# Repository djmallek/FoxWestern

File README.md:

# FoxWestern
This is for a rocketry project.  It uses tracking, remote, and onboard logging to keep track of the rocket's location and howmany G's it pulls.

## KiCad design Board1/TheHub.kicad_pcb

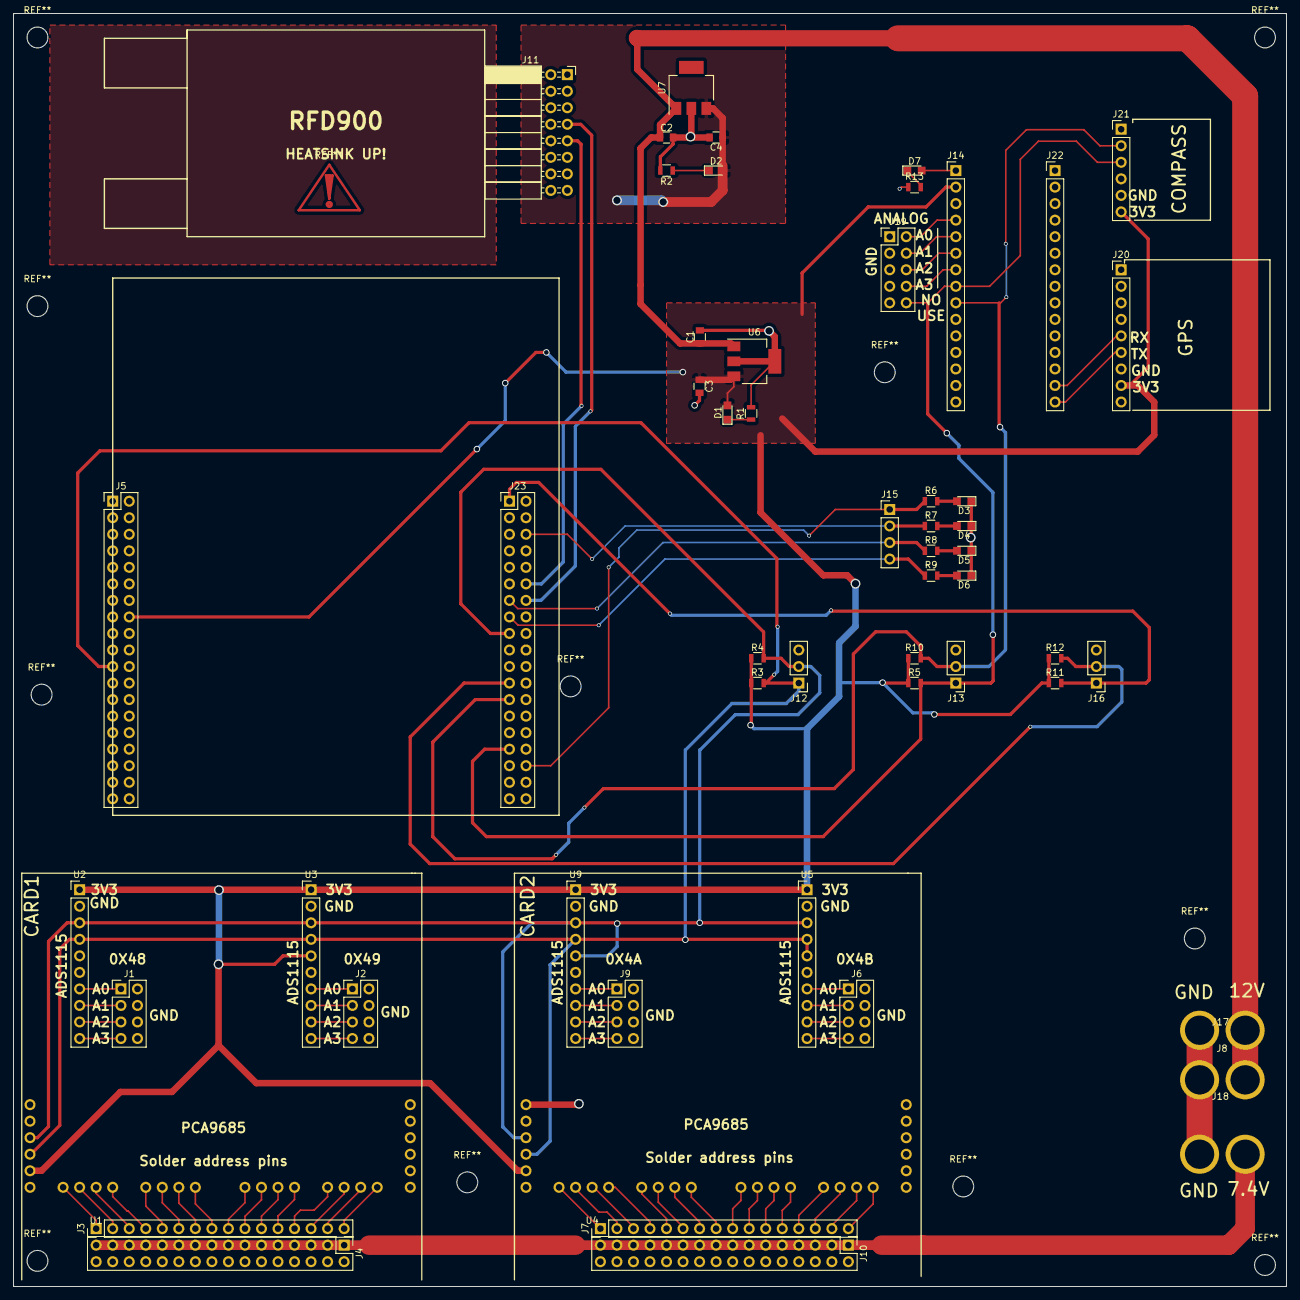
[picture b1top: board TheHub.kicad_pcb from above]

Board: 2 copper layers, 195.6 x 195.6 mm, 55 parts (0 on the bottom side), 79 nets.

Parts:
C1, C2, C3, C4: 10U; C_0805
D1, D2, D3, D4, D5, D6, D7: LED; LED_0805
J1: ARM_ADC_1; Pin_Header_Straight_2x04_Pitch2.54mm
J2: ARM_ADC_2; Pin_Header_Straight_2x04_Pitch2.54mm
J3: ARM_PWM_OUT; Pin_Header_Straight_1x16_Pitch2.54mm
J4: ARM POWER CONN; Pin_Header_Straight_2x16_Pitch2.54mm
J5: NucleoLeft; NucleoSocketStrip
J6: SCI_ADC_1; Pin_Header_Straight_2x04_Pitch2.54mm
J7: SCIENCE_PWM_OUT; Pin_Header_Straight_1x16_Pitch2.54mm
J8: 12V MAIN POWER; XT60
J9: WHEEL_ADC_1; Pin_Header_Straight_2x04_Pitch2.54mm
J10: SCIENCE + WHEELS POWER CONN; Pin_Header_Straight_2x16_Pitch2.54mm
J11: RFD900; Socket_Strip_Angled_2x08_Pitch2.54mm
J12: I2C_1 Test Point; Pin_Header_Straight_1x03_Pitch2.54mm
J13: I2C_2 Test Point; Pin_Header_Straight_1x03_Pitch2.54mm
J14: ARDUINO NANO LEFT; Socket_Strip_Straight_1x15_Pitch2.54mm
J15: GPIO Test; Pin_Header_Straight_1x04_Pitch2.54mm
J16: I2C_3 Test Point; Pin_Header_Straight_1x03_Pitch2.54mm
J17: 12V OUT; XT60
J18: 7.4V IN; XT60
J19: ANALOG SENSORS; Pin_Header_Straight_2x05_Pitch2.54mm
J20: GPS; Socket_Strip_Straight_1x09_Pitch2.54mm
J21: COMPASS; Socket_Strip_Straight_1x06_Pitch2.54mm
J22: ARDUINO NANO RIGHT; Socket_Strip_Straight_1x15_Pitch2.54mm
J23: NucleoRight; NucleoSocketStrip
R1, R2, R6, R7, R8, R9, R13: 220; R_0805
R3, R4, R5, R10, R11, R12: 2.2K; R_0805
U1, U4: PRE-PCA9685; PCA9685
U2, U3, U5, U9: PRE-ADS1115; Socket_Strip_Straight_1x10_Pitch2.54mm
U6: TL1963; SOT-223-3Lead_TabPin2
U7: LM340MP-5.0; SOT-223

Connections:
+3V3: C3.1, D1.2, J5.16, J14.2, J20.8, J21.6, R3.1, R4.1, R5.1, R10.1, R11.1, R12.1, U1.5, U2.1, U3.1, U3.5, U4.5, U5.1, U6.3, U9.1
+5V: C4.1, D2.2, J5.18, J11.4, U7.3
+12V: C1.1, C2.1, J8.1, J17.1, U6.1, U7.1
/7.4V: J4.1, J4.3, J4.5, J4.7, J4.9, J4.11, J4.13, J4.15, J4.17, J4.19, J4.21, J4.23, J4.25, J4.27, J4.29, J4.31, J10.1, J10.3, J10.5, J10.7, J10.9, J10.11, J10.13, J10.15, J10.17, J10.19, J10.21, J10.23, J10.25, J10.27, J10.29, J10.31, J18.1
/A0: J14.4, J19.2
/A1: J14.5, J19.4
/A2: J14.6, J19.6
/A3: J14.7, J19.8
/A4: J13.1, J14.8, J19.10, J21.3, J23.31, R5.2
/A5: J13.2, J14.9, J21.2, J23.25, R10.2
/D13: D7.2, J14.1
/PA6: J15.3, J23.13, R8.1
/PA7: J15.4, J23.15, R9.1
/PA8: J16.2, J23.23, R12.2
/PA11: J11.7, J23.14
/PA12: J11.9, J23.12
/PB6: J12.2, J23.17, R4.2, U1.3, U2.3, U3.3, U4.3, U5.3, U9.3, U9.5
/PB7: J5.21, J12.1, R3.2, U1.4, U2.4, U3.4, U4.4, U5.4, U5.5, U9.4
/PC4: J15.1, J23.34, R6.1
/PC5: J15.2, J23.6, R7.1
/PC9: J16.1, J23.1, R11.2
/RX0: J20.5, J22.14
/TX1: J20.6, J22.15
GND: C1.2, C2.2, C3.2, C4.2, D3.1, D4.1, D5.1, D6.1, J1.2, J1.4, J1.6, J1.8, J2.2, J2.4, J2.6, J2.8, J4.2, J4.4, J4.6, J4.8, J4.10, J4.12, J4.14, J4.16, J4.18, J4.20, J4.22, J4.24, J4.26, J4.28, J4.30, J4.32, J5.8, J5.19, J5.20, J5.22, J6.2, J6.4, J6.6, J6.8, J8.2, J9.2, J9.4, J9.6, J9.8, J10.2, J10.4, J10.6, J10.8, J10.10, J10.12, J10.14, J10.16, J10.18, J10.20, J10.22, J10.24, J10.26, J10.28, J10.30, J10.32, J11.1, J11.2, J11.16, J12.3, J13.3, J14.14, J16.3, J17.2, J18.2, J19.1, J19.3, J19.5, J19.7, J19.9, J20.7, J21.5, J22.12, J23.9, J23.20, R1.2, R2.2, R13.1, U1.1, U2.2, U2.5, U3.2, U4.1, U5.2, U6.2, U7.2, U9.2
unnamed: D1.1, R1.1
unnamed: D2.1, R2.1
unnamed: D3.2, R6.2
unnamed: D4.2, R7.2
unnamed: D5.2, R8.2
unnamed: D6.2, R9.2
unnamed: D7.1, R13.2
unnamed: J1.1, U2.7
unnamed: J1.3, U2.8
unnamed: J1.5, U2.9
unnamed: J1.7, U2.10
unnamed: J2.1, U3.7
unnamed: J2.3, U3.8
unnamed: J2.5, U3.9
unnamed: J2.7, U3.10
unnamed: J3.1, U1.7
unnamed: J3.2, U1.8
unnamed: J3.3, U1.9
unnamed: J3.4, U1.10
unnamed: J3.5, U1.11
unnamed: J3.6, U1.12
unnamed: J3.7, U1.13
unnamed: J3.8, U1.14
unnamed: J3.9, U1.15
unnamed: J3.10, U1.16
unnamed: J3.11, U1.17
unnamed: J3.12, U1.18
unnamed: J3.13, U1.19
unnamed: J3.14, U1.20
unnamed: J3.15, U1.21
unnamed: J3.16, U1.22
unnamed: J6.1, U5.7
unnamed: J6.3, U5.8
unnamed: J6.5, U5.9
unnamed: J6.7, U5.10
unnamed: J7.1, U4.7
unnamed: J7.2, U4.8
unnamed: J7.3, U4.9
unnamed: J7.4, U4.10
unnamed: J7.5, U4.11
unnamed: J7.6, U4.12
unnamed: J7.7, U4.13
unnamed: J7.8, U4.14
unnamed: J7.9, U4.15
unnamed: J7.10, U4.16
unnamed: J7.11, U4.17
unnamed: J7.12, U4.18
unnamed: J7.13, U4.19
unnamed: J7.14, U4.20
unnamed: J7.15, U4.21
unnamed: J7.16, U4.22
unnamed: J9.1, U9.7
unnamed: J9.3, U9.8
unnamed: J9.5, U9.9
unnamed: J9.7, U9.10

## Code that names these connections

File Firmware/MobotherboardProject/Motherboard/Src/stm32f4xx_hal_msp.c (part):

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  /* USER CODE END I2C1_MspInit 0 */
  
    /**I2C1 GPIO Configuration    
    PB6     ------> I2C1_SCL
    PB7     ------> I2C1_SDA 
    */
    GPIO_InitStruct.Pin = GPIO_PIN_6|GPIO_PIN_7;
    GPIO_InitStruct.Mode = GPIO_MODE_AF_OD;
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  /* USER CODE END I2C3_MspInit 0 */
  
    /**I2C3 GPIO Configuration    
    PC9     ------> I2C3_SDA
    PA8     ------> I2C3_SCL 
    */
    GPIO_InitStruct.Pin = GPIO_PIN_9;
    GPIO_InitStruct.Mode = GPIO_MODE_AF_OD;
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    __HAL_RCC_I2C1_CLK_DISABLE();
  
    /**I2C1 GPIO Configuration    
    PB6     ------> I2C1_SCL
    PB7     ------> I2C1_SDA 
    */
    HAL_GPIO_DeInit(GPIOB, GPIO_PIN_6|GPIO_PIN_7);

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    __HAL_RCC_I2C3_CLK_DISABLE();
  
    /**I2C3 GPIO Configuration    
    PC9     ------> I2C3_SDA
    PA8     ------> I2C3_SCL 
    */
    HAL_GPIO_DeInit(GPIOC, GPIO_PIN_9);

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    __HAL_RCC_USART6_CLK_ENABLE();
  
    /**USART6 GPIO Configuration    
    PA11     ------> USART6_TX
    PA12     ------> USART6_RX 
    */
    GPIO_InitStruct.Pin = GPIO_PIN_11|GPIO_PIN_12;
    GPIO_InitStruct.Mode = GPIO_MODE_AF_PP;
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    __HAL_RCC_USART6_CLK_DISABLE();
  
    /**USART6 GPIO Configuration    
    PA11     ------> USART6_TX
    PA12     ------> USART6_RX 
    */
    HAL_GPIO_DeInit(GPIOA, GPIO_PIN_11|GPIO_PIN_12);

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
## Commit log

2017-06-05 Initial commit, Add nucleo pinout slot, and nucleo resources
2017-06-06 Add PCA9685, ADS1115, and hookups for different parts on i2c bus
2017-06-06 Add Pre-PCA9685 footprint
2017-06-06 Add STM32Cube files, add basic UART communication eaxample, add HAL references
2017-06-06 Add support for RFD900 on USART6
2017-06-06 Change I2C lines to properly index
    I2C starts at 1, not 0
2017-06-06 Add support for I2C123, add test pins for I2C, add 4 GPIO status LEDs with test pins
2017-06-06 Add 5v regulator for RFD900, add power status LEDs fro 5v and 3v3
2017-06-06 Add additional inputs to autonomy section
2017-06-06 Add option for second external regulated voltage, add connections for servo power on wheels, science, and arm cards
2017-06-07 Add support for compass on I2C_2, provide prodcut specific guidlines for sensor compatibility
2017-06-07 Add XT60 connector, split nano into 2 pieces
2017-06-07 Create cvpcb assiciation, generate netlist
2017-06-07 Init PCB layout
    Spread out footprints. TODO: Make changes to nucleo harness
2017-06-09 Change 3v3 regulator, change appropriate pins to sockets
2017-06-09 Create Layout placement forRFD900 and Nucleo
2017-06-09 Determine Main Board Layout
2017-06-09 Update nucleo headers to correct pin assignment
2017-06-09 Finish Layout
    RFD900 Is given insulated copper island to act as a heat spreader
2017-06-09 Add silkscreen labeling
2017-06-10 Add M3 Mouting Holes
2017-06-10 Generate Gerbers
2017-06-10 Add logo to PCB
2017-06-11 Test #1: Webhooks
2017-06-11 Test Webhooks
2017-06-18 Serial comms works
2017-06-18 Remove test file
2017-06-19 Add button press functionality
2017-06-19 I2C communication works
2017-07-12 I2C works and is Tested

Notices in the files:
Firmware/MobotherboardProject/Motherboard/Src/stm32f4xx_hal_msp.c:
COPYRIGHT(c) 2017 STMicroelectronics
(C) COPYRIGHT STMicroelectronics *****END OF FILE
